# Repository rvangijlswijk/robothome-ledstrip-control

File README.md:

# robothome-ledstrip-control
RobotHome project: control a ledstrip either via pushbutton or over WiFi

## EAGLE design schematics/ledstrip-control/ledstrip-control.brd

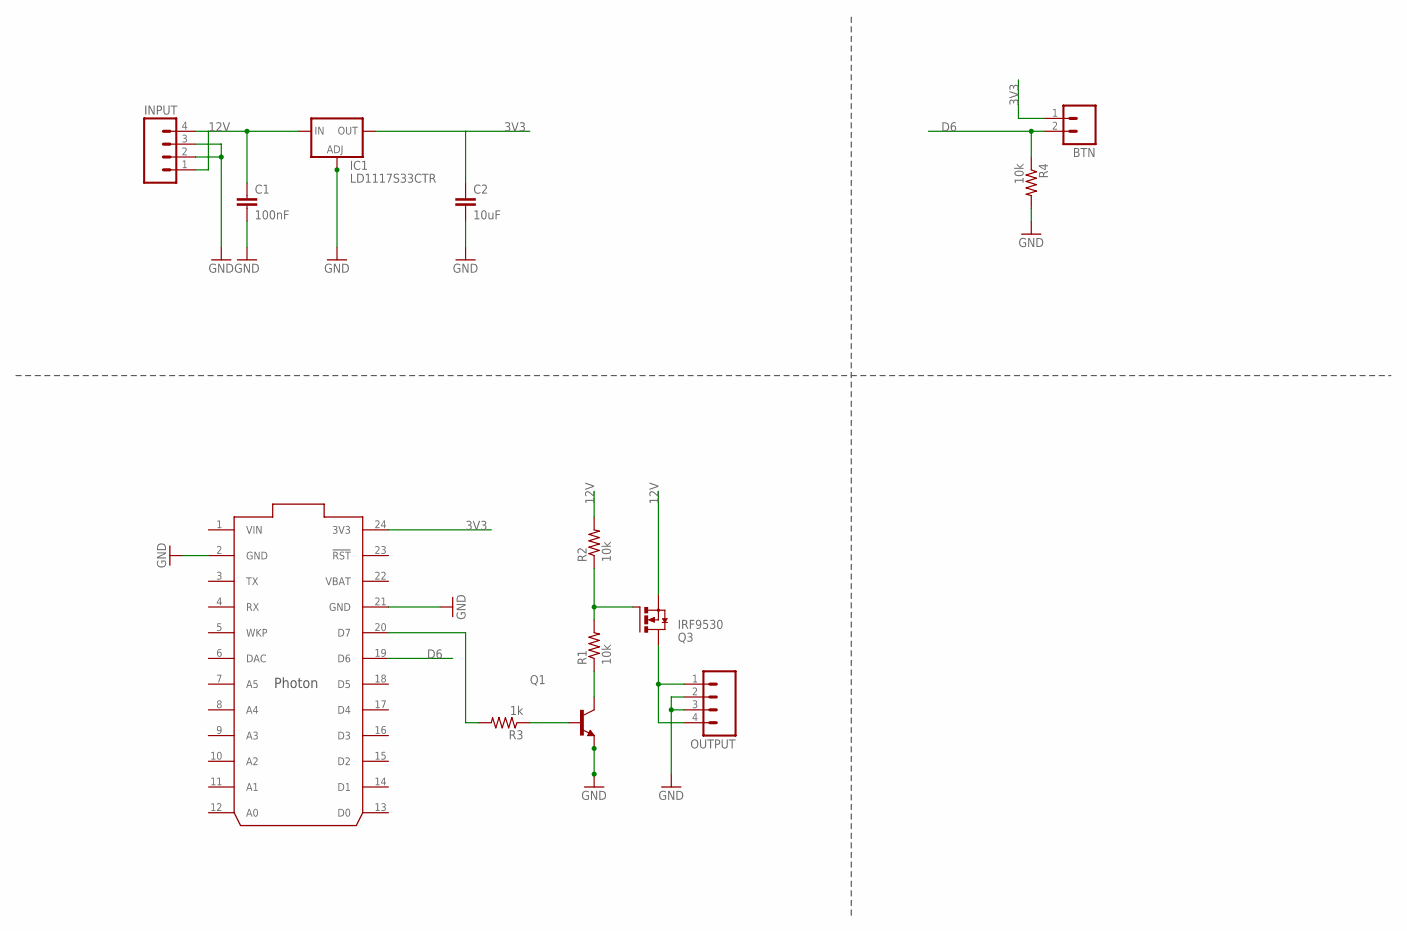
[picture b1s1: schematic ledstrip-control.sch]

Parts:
BTN: M02PTH; 1X02
C1: 100nF; CAP-PTH-SMALL
C2: 10uF; CAP-PTH-SMALL
IC1: LD1117S33CTR; SOT223; FARNELL 1467779
INPUT: M04PTH; 1X04
OUTPUT: M04PTH; 1X04
Q1: 2N2222-NPN-TO18-EBC; TO18
Q3: IRF9530; D2PACK; FARNELL 9103155
R1, R2, R4: 10k; AXIAL-0.3
R3: 1k; AXIAL-0.3
U1: PHOTON_WITH_HEADERS; PHOTON

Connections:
3V3: BTN.1, C2.1, IC1.4 (OUT), U1.24 (3V3)
12V: C1.1, IC1.3 (IN), INPUT.1, INPUT.4, Q3.3 (S), R2.P$2 (2)
D6: BTN.2, R4.P$1 (1), U1.19 (D6)
GND: C1.2, C2.2, IC1.1 (ADJ), INPUT.2, INPUT.3, OUTPUT.2, OUTPUT.3, Q1.1 (E), R4.P$2 (2), U1.2 (GND), U1.21 (GND)
unnamed: OUTPUT.1, OUTPUT.4, Q3.2 (D)
unnamed: Q3.1 (G), R1.P$2 (2), R2.P$1 (1)
unnamed: Q1.3 (C), R1.P$1 (1)
unnamed: Q1.2 (B), R3.P$1 (1)
unnamed: R3.P$2 (2), U1.20 (D7)
VBAT: U1.22 (VBAT)
VIN: U1.1 (VIN)

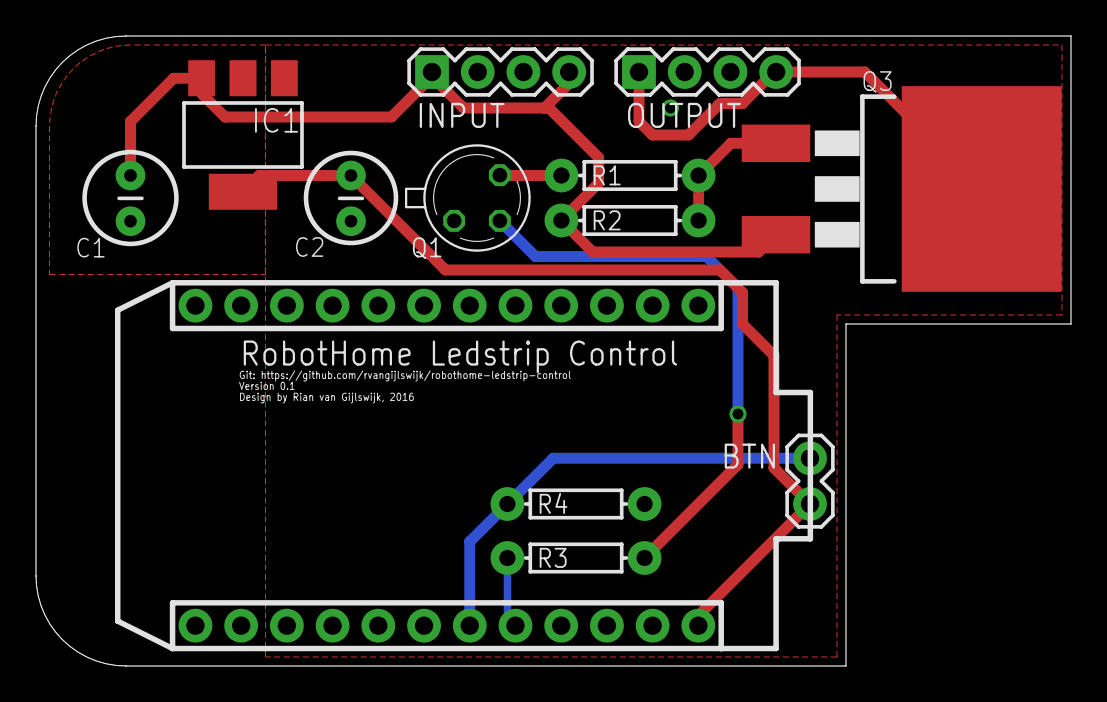
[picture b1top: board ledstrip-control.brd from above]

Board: 2 copper layers, 57.5 x 35.0 mm, 13 parts (0 on the bottom side), 9 nets.

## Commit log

2016-06-01 Removed backup files
2016-06-01 Added gitignore
2016-06-01 Prepared pcb design for ordering

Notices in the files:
parts and their libraries:
SparkFun-Passives: Licensing: Creative Commons ShareAlike 4.0 International - https://creativecommons.org/licenses/by-sa/4.0
